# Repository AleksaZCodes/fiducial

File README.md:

# Fiducial

<!-- fid:describes thesis.toml -->
> **Build any robust multidisciplinary product with AI agents.**

That is the platform's thesis ([`thesis.toml`](thesis.toml), `fid thesis`). How:
**declare each fact once, derive every artifact from it**, and gate the result.
<!-- fid:end-describes -->

Fiducial is a cross-domain build system for products that span **web, firmware,
electronics, mechanical, simulation and content** — built at the quality and pace
that normally needs a team, by one person working with agents.

Not by working harder at each domain. By deleting the work that exists only
because the domains don't talk to each other.

---

## The problem it removes

In a cross-domain product the same fact gets written down many times:

- a **pin assignment** — in the schematic, the firmware, the test rig, the docs
- a **protocol message** — in the firmware, and again in the web client
- a **board dimension** — in the PCB tool, the enclosure model, the marketing render

Every duplicate is a place where reality drifts from itself. Drift is discovered
late, in the field, expensively.

So: **one declaration, many derivations.** The declaration is typed,
machine-readable and lives in git. Everything downstream is generated, and
generated artifacts are never hand-edited.

## The shape of the system

Three ideas stacked, and each one exists to make the one above it cheap.

```
                        ┌───────────────────────────────┐
   DECLARE              │  board.interface.json         │   typed facts,
   a fact, once         │  fiducial.toml  ·  messages/  │   inert, in git
                        └───────────────┬───────────────┘
                                        │
                                  fid derive          ← gated by --check
                                        │
        ┌───────────────┬───────────────┼───────────────┬───────────────┐
        ▼               ▼               ▼               ▼               ▼
   DERIVE          enclosure       TypeScript      wrangler.toml    migrations
   every artifact  STL · GLB       types           (deploy cfg)     SQL schema
        │
        └── never hand-edited · hashed into fiducial.lock · stale ⇒ CI fails

        firmware · desktop · browser · edge · CLI     ← many runtimes
                          ╲   │   ╱
   RUN IT ANYWHERE  fiducial-protocol                  ← one waist
                          ╱   │   ╲
        USB serial · Web Serial · WebUSB · BLE · LoRa  ← many transports
```

Logic lives as far down as it can. The `no_std` Rust spine compiles for the host,
`wasm32`, and two embedded targets **on every commit** — so a behaviour written
once runs in a browser, on a desktop, at the edge, and on a microcontroller, and
outlives every framework above it.

## A worked example

```sh
cargo install fiducial-cli

fid new my-product && cd my-product
fid add capability hardware   # one declaration → case, board, schematic, BOM, interface
fid add capability firmware-rp2040
fid derive                    # run every pipeline, hash every output
fid dash                      # roadmap, decisions, CI, pipelines, freshness
```

Declare the product once, in `hardware/product.toml`: its outline, its parts,
and what each pin connects to (an excerpt):

```toml
[[part]]
id     = "mcu"
symbol = "MCU_RaspberryPi:RP2040"
pins   = { GPIO4 = "SENSOR_SDA", GPIO5 = "SENSOR_SCL", GND = "GND" }

[[part]]
id   = "r-sda"
pick = { category = "Resistors", package = "0603", value = "4k7", has = ["1%"] }  # resolved to a real LCSC part, locked
pins = { 1 = "SENSOR_SDA", 2 = "3V3" }

[firmware]
mcu = "mcu"
```

Then `fid derive` produces — with nobody modelling, drawing or copying anything —

- the **case** around the parts, with every socket's window cut, and the
  **board** inside it: placed by a constraint solver, every pad on its net;
- the **schematic**, and the **BOM**, each part's LCSC number taken from
  `hardware/parts.lock`;
- `interface.ts` — the nets as a **TypeScript type**, for the app that talks
  to the device;
- `board.rs` — the **firmware's pin map**: `board::sensor_sda!(p)` is
  `p.PIN_4`.

`hardware/build.sh` then routes the board, builds every solid, checks that
it all fits and goes together, and writes the files a board house needs to
make and assemble it.

Move `SENSOR_SDA` to `GPIO6` and the copper, the schematic and the firmware
move with it — the firmware with no edit. Rename it, and firmware or web code
still using the old name stops compiling. Until `fid derive` has run,
`fid derive --check` names every artifact that no longer matches the
declaration and exits non-zero. It runs in CI, so an artifact that did not
follow its declaration fails the build instead of shipping. That is the whole
contract.

The whole of it, on a real product: [`examples/sensor-stick/`](examples/sensor-stick)
is a USB-C temperature and humidity stick — case, routed board, orderable fab
files, firmware and a web page from one declaration, built end to end in CI —
and [how it was made](docs/guides/sensor-stick.md), step by step.

## What you can add to it

Nothing above is special-cased into the CLI. Each of these is a **capability** —
a named, versioned extension that contributes declarations, pipelines, guard
rules and a skill for agents. `fid new` generates none of them; you add what the
product actually needs.

<!-- fid:begin capabilities -->
| Capability | Contributes | Install |
|---|---|---|
| `adapters` | declares `adapters`; 1 pipeline(s); seeds a `fiducial.toml` block | `fid add capability adapters` |
| `brand` | declares `brand`; 2 pipeline(s); 2 template file(s); seeds a `fiducial.toml` block | `fid add capability brand` |
| `cms` | declares `cms`; 1 pipeline(s); 6 template file(s); seeds a `fiducial.toml` block | `fid add capability cms` |
| `content` | declares `content.toml`, `content/posts/en/hello.md`; 1 pipeline(s); 2 template file(s) | `fid add capability content` |
| `deploy` | declares `deploy`; 1 pipeline(s); seeds a `fiducial.toml` block | `fid add capability deploy` |
| `design` | declares `design-system.md`; 1 pipeline(s); 4 template file(s) | `fid add capability design` |
| `eda` | declares `board/board.interface.json`; 2 pipeline(s); 1 template file(s) | `fid add capability eda` |
| `firmware-rp2040` | 11 template file(s); guard rules | `fid add capability firmware-rp2040` |
| `firmware-stm32` | 10 template file(s); guard rules | `fid add capability firmware-stm32` |
| `hardware` | declares `hardware/outline.svg`, `hardware/product.toml`; 1 pipeline(s); 12 template file(s) | `fid add capability hardware` |
| `i18n` | declares `i18n`, `messages/en.json`, `messages/sr.json`; 1 pipeline(s); 2 template file(s); seeds a `fiducial.toml` block | `fid add capability i18n` |
| `identity` | declares `identity`; 1 pipeline(s); seeds a `fiducial.toml` block | `fid add capability identity` |
| `legal` | declares `legal`; 1 pipeline(s); 2 template file(s); seeds a `fiducial.toml` block | `fid add capability legal` |
| `migrations` | declares `migrations`; 1 pipeline(s) | `fid add capability migrations` |
| `monitoring` | declares `monitoring.toml`; 1 pipeline(s) | `fid add capability monitoring` |
| `press` | declares `press`, `press/docs/en/boilerplate.md`, `press/docs/en/facts.md`, `press/stories/en/0001-why-this-exists.md`; 1 pipeline(s); 2 template file(s); seeds a `fiducial.toml` block | `fid add capability press` |
| `protocol` | declares `protocol.toml`; 1 pipeline(s) | `fid add capability protocol` |
| `realtime` | a skill | `fid add capability realtime` |
| `research` | declares `paper`; seeds a `fiducial.toml` block | `fid add capability research` |
| `seo` | declares `seo`; 1 pipeline(s); 2 template file(s); seeds a `fiducial.toml` block | `fid add capability seo` |
| `tauri` | 5 template file(s); guard rules | `fid add capability tauri` |
| `topology` | declares `topology.toml`; 1 pipeline(s) | `fid add capability topology` |
| `web-next` | 13 template file(s); guard rules | `fid add capability web-next` |
| `web-svelte` | 11 template file(s); guard rules | `fid add capability web-svelte` |
| `worker-cloudflare` | 1 template file(s); guard rules | `fid add capability worker-cloudflare` |
<!-- fid:end capabilities -->

### A physical product, from one file

`hardware` is the capability that goes furthest. One `hardware/product.toml`
names an outline in any SVG (a logo works), the regions on it, and the parts —
each a real KiCad symbol, footprint and STEP model, with its LCSC number and
its datasheet. `fid derive` solves the case round them, sizes and sections the
board, places its parts with a constraint solver (OR-Tools CP-SAT — every rule
a constraint, and a contradiction named rather than guessed at), wires every
pin to its net, and writes a gated layout, BOM, KiCad board and schematic. `hardware/build.sh`
then routes and DRCs the board (Freerouting), builds the solid model and fails
on any interference, unsealed joint or part that cannot go in, and exports
Gerbers, STEP and a review pack of renders. Where the vocabulary stops, a
product adds its own geometry (`hardware/shapes.py`) or its own STEP model,
and the checks still run over it.

Everything a part needs travels with it, in KiCad's own library layout:
`hardware/lib/` holds the symbols, footprints, models and datasheets (with
text copies), hash-checked, and `hardware/lib/PARTS.md` puts every part on one
page — what it is, its files, every pin's net — as the context a person or an
agent starts from.

<!-- fid:describes crates/fiducial-cli/src/adapter.rs#pub static CONTRACTS -->

Vendors sit behind **adapter contracts**, chosen per product in `[adapters]`.
Every contract ships with `none` — a real, working implementation, not a
placeholder, which is what makes it cost nothing to wire in from the first
commit. A name under *Planned* cannot be selected and fails with a message
saying so: a selectable name with nothing behind it is a promise the platform
does not keep.

Three of those `none`s **fail rather than succeed silently**: `auth`, `ai` and
`systemOne`. The difference is whether the caller reads a result. A no-op send
or enqueue is indistinguishable from the real thing at the call site — the
caller wanted an effect elsewhere. A session, a completion and a decision *are*
the result, so returning a fabricated one turns "no vendor selected" into a
logged-in stranger, a blank answer in the UI, or a confidently wrong branch
taken in production — and all three get debugged as bugs somewhere else. They
still cost nothing to wire in: constructing them is free, and nothing fails
until something actually asks.

<!-- fid:end-describes -->

<!-- fid:begin adapters -->
| Contract | For | Selectable today | Planned |
|---|---|---|---|
| `database` | Relational storage: queries, migrations, transactions | `none`, `d1`, `supabase` | `neon`, `postgres` |
| `storage` | Object storage: put, get, signed URLs | `none`, `r2`, `supabase-storage` | `s3` |
| `deploy` | Where the product ships and how a release is promoted | `none`, `cloudflare` | `vercel`, `fly` |
| `email` | Transactional email: send, template, verify a domain | `none`, `resend` | `ses`, `cloudflare-email` |
| `newsletter` | Subscriber list management: subscribe, unsubscribe, status | `none`, `resend` | — |
| `errors` | Error tracking and diagnostics | `none` | `sentry`, `workers-analytics` |
| `botProtection` | Bot / abuse challenge verification | `none`, `turnstile` | `recaptcha`, `hcaptcha` |
| `queue` | Asynchronous job/message queue (producer side) | `none`, `cloudflare-queues` | `sqs` |
| `ai` | Language-model calls: chat, streaming, tool use | `none`, `openrouter` | `workers-ai`, `anthropic`, `openai` |
| `auth` | Users and authentication: sign-up, sign-in, sessions | `none`, `supabase` | `clerk`, `auth.js` |
| `systemOne` | Typed probabilistic decisions: yes/no, one-of-N, ordered levels | `none`, `openrouter`, `typesafe` | — |
<!-- fid:end adapters -->

Both tables are generated from the registries that enforce them, by
`fid context`, and CI fails if they drift from the code.

## How you extend it

### A capability is a directory

There is no plugin API to learn and no CLI release to wait for. The **layout is
the manifest** — `fid` derives the capability from the directory, and a
third-party capability goes through the same derivation, the same conformance
checks and the same lock entry as a built-in.

```
my-capability/
├── SKILL.md              ← the only required file: how an agent uses this
├── capability.toml       ← optional: description, guard rules, [config] seed,
│                           declared directories, required adapter contracts
├── declarations/         ← typed facts, installed at the path below this dir
│   └── messages/en.json
├── pipelines/
│   └── i18n.toml         ← name, executor, args, outputs
└── anything-else         ← a plain template file, copied in, gated by nothing
```

Scaffold one, then install it from anywhere — a directory, or a git repository
pinned in `fiducial.lock` at the commit it resolved to:

```sh
fid capability new my-sensor                    # scaffold the directory above

fid add capability my-sensor --from ./capabilities/my-sensor
fid add capability stripe    --from git:https://github.com/acme/fid-stripe#v1.2.0
fid capability check                            # conformance, once installed
```

One file is a complete capability. The failure mode for an extension system is
ceremony, so `capability.toml` is optional and a capability without one takes
its description from the first line of prose in its own skill.

### The seven kinds, and why the difference is not cosmetic

<!-- fid:describes crates/fiducial-cli/src/capability/manifest.rs#pub fn derive -->

| Kind | Is | Example |
|---|---|---|
| **Declaration** | a typed fact, written once, inert — a file, a `fiducial.toml` block, or a directory the product fills | `hardware/product.toml`, the `[i18n]` block, `migrations/` |
| **Pipeline** | reads declarations, produces artifacts, **gated by `fid derive --check`** | `pipelines/hardware.toml` |
| **Adapter** | a swappable vendor behind a fixed contract | `storage = "r2"` |
| **Tool** | an external command the capability's work needs on PATH — declared, never installed | `requires_tools = ["wrangler"]` |
| **Prerequisite** | another capability this one cannot work without — checked at install, not at first failure | `requires_capabilities = ["i18n"]` |
| **Template** | a plain file copied in, belonging to no pipeline | `apps/worker/wrangler.toml` |
| **Scoped template** | a template under `for/<capability>/`, installed only alongside that capability | `for/web-svelte/…/LocalePicker.svelte` |

<!-- fid:end-describes -->

The test for a declaration: *could two different pipelines read this and both be
correct?* If yes it is a declaration; if it is one tool's config file it is a
template.

The test for a **scoped** template: *would this file be dead weight in a
product that has this capability but not the other one?* A React component in
a SvelteKit app is the case it exists for. Install order does not matter —
adding the target capability later back-fills what the others were holding.

Filing one as another is not a style mistake. A pipeline outside `pipelines/` is
installed and never runs; a `pipelines/` file listed as a template is installed
and never gated. `fid capability check` rejects both.

### A pipeline is four lines

```toml
name     = "enclosure"
executor = "fid-mesh"
args     = ["board/board.interface.json"]
outputs  = [
  "enclosure/case-base.stl",
  "enclosure/case-lid.stl",
  "enclosure/gasket.stl",
  "enclosure/case.glb",
]
```

`outputs` is what makes it gated: `fid derive` hashes each one into
`fiducial.lock`, and `fid derive --check` fails when a hash no longer matches
what the declaration implies.

`inputs` closes the other half. An output can match its hash while the file it
was derived *from* has moved — a logo redrawn, a schema another tool rewrote —
and nobody re-derived. Files listed in `inputs` (and those a built-in executor
knows it reads, such as the SVGs a `hardware/product.toml` addresses) are
hashed into the lock too, and `--check` names the one that moved.

<!-- fid:describes crates/fiducial-cli/src/commands/derive.rs#fn run_pipeline_command -->

Executors are `shell` and `cargo-test` — which need no platform change at all —
plus the in-process ones (`fid-validate`, `fid-mesh`, `fid-i18n`, `fid-brand`,
`fid-thesis`, `fid-deploy`, `fid-identity`, `fid-adapters`, `fid-schema`,
`fid-legal`, `fid-design`, `fid-protocol`, `fid-topology`, `fid-monitoring`, `fid-hardware`). Reach for `shell` first; a new in-process executor
is warranted only when the work is genuinely a Rust library call rather than a
tool invocation.

A `shell` pipeline that runs `node` runs under Node's permission model: it may
read its script's directory, its own `pipelines/<name>.toml`, its declared
`inputs` and `node_modules`, and write only where its `outputs` go. A script
that reads a file it does not declare fails naming that file, instead of
producing an output whose input the lock never recorded.

`fid-design` is the clearest case of that line: it parses a declaration, runs
OKLCH-to-sRGB conversion and WCAG contrast arithmetic over the palette, and
fails the derive when a declared pair misses its minimum. Shelling out would
mean shipping a script and a language runtime to do arithmetic the binary
already can.

<!-- fid:end-describes -->

### Adding a vendor to a contract

Implement the contract in `crates/fiducial-adapters` (and its TypeScript mirror
in `packages/adapters`), then move the vendor from `candidates` to
`implementations` in `crates/fiducial-cli/src/adapter.rs`. The table above and
the error message a user sees both derive from that one move.

One place does need the new name: `REAL_VENDORS` in
`packages/adapters/src/generated-factory.test.js`, which is the list of vendor
selections CI actually compiles the generated factory for. A vendor missing
from it is generated and never typechecked, so the suite names itself in that
comment rather than leaving it to be discovered.

Deeper detail: [`docs/specs/2026-09-15-external-capabilities.md`](./docs/specs/2026-09-15-external-capabilities.md)
and [`docs/specs/2026-09-14-capability-taxonomy.md`](./docs/specs/2026-09-14-capability-taxonomy.md).

## Documentation

**New here?** [Start here](./docs/guides/start-here.md) explains what this is and
why it is shaped that way, then [Your first product](./docs/guides/first-product.md)
takes you from nothing to a generated enclosure and a CI gate in about twenty
minutes.

| Read | For |
|---|---|
| [**docs/guides/**](./docs/guides/) | Step-by-step guides for humans and agents |
| [`AGENTS.md`](./AGENTS.md) | Working here as an agent — layout, rules, build commands |
| [`MISSION.md`](./MISSION.md) | Why this exists. The tiebreaker for ambiguous decisions. |
| [`ARCHITECTURE.md`](./ARCHITECTURE.md) | How the layers fit together. |
| [`STACK.md`](./STACK.md) | Every technology choice, enumerated. |
| [`ROADMAP.md`](./ROADMAP.md) | What is intended, in order — and so what is next. |
| [`SHIPPED.md`](./SHIPPED.md) | What was built, phase by phase. |
| [`docs/protocol/`](./docs/protocol/) | The wire specification + conformance vectors. |
| [`docs/specs/`](./docs/specs/) | Design decisions, append-only. |

Each crate and package carries its own README — start with
[`fiducial-cli`](./crates/fiducial-cli) if you want to build something, or
[`fiducial-core`](./crates/fiducial-core) if you want to see the spine.

## Repository

`firmware/` is a separate Cargo workspace (Embassy; RP2040 + STM32), and `docs/`
holds the specs, the protocol and the compatibility matrix. The two workspaces
this repository builds:

<!-- fid:begin layout -->
```
fiducial/
├── crates/               15 members
│   ├── fiducial                 Declare each fact once. Derive every artifact from it.
│   ├── fiducial-adapters        Cross-platform adapter contracts for Fiducial — database, s…
│   ├── fiducial-cli             fid — the Fiducial platform CLI
│   ├── fiducial-core            no_std spine: IDs, time primitives, validation, state machi…
│   ├── fiducial-eda             no_std EDA pipeline types — the BoardInterface schema for b…
│   ├── fiducial-geometry        no_std geometry for Fiducial: points, tolerance profiles, c…
│   ├── fiducial-identity        no_std identity spine: one Principal across users, devices…
│   ├── fiducial-mesh            no_std case generation from a board outline: gasket-sealed…
│   ├── fiducial-model           no_std Fact, Decision and Pipeline contract types.
│   ├── fiducial-ota             no_std over-the-air firmware update protocol: signed manife…
│   ├── fiducial-protocol        no_std transport-agnostic protocol: framing, checksums, seq…
│   ├── fiducial-quantity        no_std typed quantities with tolerance algebra and assertions.
│   ├── fiducial-sim             Numerical simulation — ODE integration that runs native (wi…
│   ├── fiducial-tauri           Serial transport and device discovery for Fiducial Tauri apps.
│   └── fiducial-wasm            WASM bindings for fiducial-core — browser, edge, and Cloudf…
└── packages/             13 members
    ├── adapters                 Cross-platform adapter contracts for Fiducial — database, s…
    ├── advisor                  Advisory checks for Fiducial — typed judgments where determ…
    ├── board-schema             TypeScript types for board.interface.json — mirrors the Rus…
    ├── cli                      fid — the Fiducial platform CLI
    ├── fiducial                 Declare each fact once. Derive every artifact from it.
    ├── headless                 Framework-agnostic headless utilities for Fiducial — Result…
    ├── i18n                     Localized by construction — typed message keys, locale nego…
    ├── identity                 One identity model across users, devices and services — mir…
    ├── realtime                 Supabase Realtime typed wrappers — Broadcast, Presence, and…
    ├── tokens                   Design tokens for Fiducial — OKLCH theme vars, Tailwind v4…
    ├── transport-web            Web Serial, WebUSB, and BLE transports for Fiducial — same…
    ├── viewer3d-react           React component for rendering Fiducial board GLB files in a…
    └── wasm-bridge              Generated TypeScript types for the fiducial WASM boundary.
```
<!-- fid:end layout -->

## License

MIT — see [`LICENSE`](./LICENSE).

Product repos, domain logic, novel protocols and hardware designs are private;
see [`IP-POLICY.md`](./IP-POLICY.md).

Contributions are welcome and need a sign-off — see [`CLA.md`](./CLA.md). It
exists so the project keeps the option to relicense later: that option is
destroyed silently by the first contribution merged without one, and cannot be
recovered afterwards.

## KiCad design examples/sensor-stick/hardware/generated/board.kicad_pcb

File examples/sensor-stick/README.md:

# sensor-stick

A USB-C stick that reports room temperature and humidity to a web page — a
whole product, from one declaration, built with
[Fiducial](https://github.com/AleksaZCodes/fiducial) and checked in its CI.

It is the platform's worked example: small and cheap (an RP2040, an AHT20
sensor, a WS2812B LED behind a 5 V buffer, a USB-C socket: 23 parts, $4.74
of them per board at five boards, LCSC's prices with minimum orders, checked
against a $15 ceiling on every derive; the printed case and the vent are not
priced), but it carries every discipline a product has — a printed case, a
routed board, firmware and a web page — and every one of them is derived
from, or checked against, the same facts.

**Status: designed and checked, not built.** Every part is a real,
orderable part, the board routes and passes KiCad's DRC, the firmware
compiles and the page type-checks. Nobody has ordered it, soldered it or
plugged it in. What would be learnt on the bench is not claimed here.

| | | |
|---|---|---|
|  |  |  |
| assembled: 36 × 84 × 15.5 mm, the USB-C socket flush with the case at one end, the sensor's vent at the other | the routed board in the base: the sensor alone at the far end, under its chimney | lid, board, base |

Renders from `hardware/build.sh`, copied to `hardware/showcase/`.

## What a person writes

| File | Is |
|---|---|
| [`hardware/product.toml`](hardware/product.toml) | the product: its outline, its case, every part (an LCSC number, a KiCad symbol and footprint) and what each pin connects to |
| [`hardware/outline.svg`](hardware/outline.svg) | the stick's shape, seen from above |
| [`hardware/vendor/`](hardware/vendor) | parts KiCad has no entry or no 3D model for, from LCSC's library (`parts.py fetch`), and the USB-C socket: KiCad's land pattern with LCSC's model on it, with where each came from |
| [`firmware/rp2040/src/main.rs`](firmware/rp2040/src/main.rs), [`firmware/shared/src/lib.rs`](firmware/shared/src/lib.rs) | the firmware: read the sensor once a second, send the reading as a fiducial-protocol frame over USB serial, colour the LED |
| [`web/src/`](web/src) | the page: connect over Web Serial, show the reading |
| [`protocol.toml`](protocol.toml) | the reading's payload — its kind byte and fields — declared once for both sides of the USB link |

## What is derived from it

`fid derive` (gated by `fid derive --check`):

| File | Is |
|---|---|
| `hardware/generated/layout.json` | every position and size, and `why` — what set each |
| `hardware/generated/placement.json` | the board placement, solved by a constraint solver (CP-SAT) |
| `hardware/generated/board.kicad_pcb`, `board.kicad_sch` | the board with every footprint placed and every pad on its net; the schematic |
| `hardware/generated/bom.csv`, `assembly.md` | the bill of materials; the order it goes together in |
| `hardware/generated/interface.ts` | the nets as a TypeScript type — the page imports it |
| `hardware/generated/board.rs` | the firmware's pin map: `board::sensor_sda!(p)` is `p.PIN_4` — the firmware takes every pin through it, and a pin named directly fails derive |
| `protocol/messages.rs`, `protocol/messages.ts` | the reading's encoder for the firmware and decoder for the page, from the same table — they cannot disagree |
| `hardware/generated/assembly.md` → why | the USB-C CC voltage each kind of source reads, solved from the pull-downs and checked against the Type-C spec's window — a wrong resistor fails derive |

`hardware/build.sh` (built, checked, not committed): the routed and
DRC-checked board, the case as STEP and STL, the fit and assembly checks,
and `hardware/build/fab/` — Gerbers, the assembly BOM and the placement file
a board house takes.

`python3 hardware/parts.py resolve` checked every LCSC number against LCSC's
own record of it and wrote what it found to `hardware/parts.lock`.

## Change one thing

Move the sensor's data line from `GPIO4` to `GPIO6` in `product.toml`:

1. `fid derive --check` fails: the board, the schematic, the interface and
   `board.rs` no longer match the declaration.
2. `fid derive` moves the copper, relabels the schematic and rewrites
   `board.rs`.
3. The firmware does not compile — and should not: GPIO6 is not one of
   I2C0's SDA pins, and Embassy's types say so. Move it to `GPIO8` instead
   (I2C0 SDA) and the firmware compiles with no edit to it.

Rename the net `SENSOR_SDA` and every line of firmware or page code that
still uses the old name stops compiling. Nothing is copied by hand, so
nothing can be left behind.

## Build it

```sh
fid derive                                   # the gated artifacts
python3 hardware/parts.py sync               # vendor symbols, footprints, models
hardware/build.sh                            # route, solids, checks, fab files, renders
(cd firmware/rp2040 && cargo build --release) # the firmware (thumbv6m-none-eabi)
(cd firmware && cargo test -p firmware-shared --target x86_64-unknown-linux-gnu)
node --experimental-strip-types --test web/src/reading.test.ts
npx esbuild web/src/main.ts --bundle --format=esm --outfile=web/dist/main.js --tsconfig=web/tsconfig.json
```

Then serve `web/` and open `index.html` in Chrome or Edge.

The first flash needs no programmer: an RP2040 with empty flash starts its
USB bootloader, and `elf2uf2-rs` or `picotool` copies the firmware across.

## How it was made

With the commands above and an agent: the walk-through, step by step — what
was typed, what the agent changed, what the gates refused and why — is
[`docs/guides/sensor-stick.md`](../../docs/guides/sensor-stick.md).

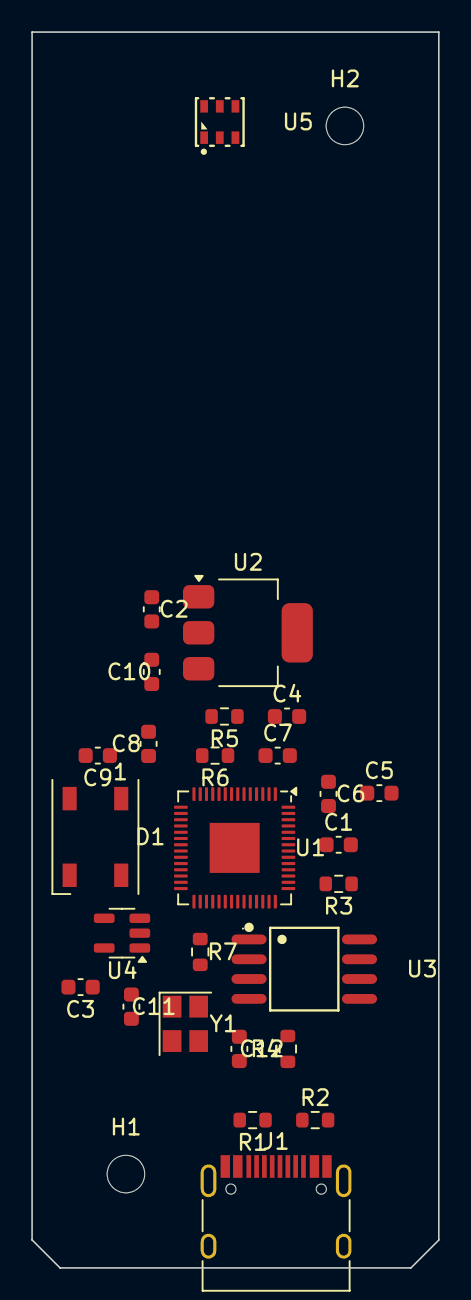
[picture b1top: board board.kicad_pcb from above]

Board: 2 copper layers, 26.0 x 79.0 mm, 29 parts (0 on the bottom side), 23 nets, no tracks yet.

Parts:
C1, C2, C3, C4, C5, C6, C7, C8, C9, C10, C11, C12: C_0603_1608Metric
D1: LED_WS2812B_PLCC4_5.0x5.0mm_P3.2mm
H1, H2: MountingHole
J1: USB_C_Receptacle_HRO_TYPE-C-31-M-12
R1, R2, R3, R4, R5, R6, R7: R_0603_1608Metric
U1: QFN-56-1EP_7x7mm_P0.4mm_EP3.2x3.2mm
U2: SOT-223-3_TabPin2
U3: SOIC-8_L5.3-W5.3-P1.27-LS8.0-BL
U4: SOT-23-5
U5: SENSOR-SMD_L3.0-W3.0-P1.00-BR
Y1: Crystal_SMD_3225-4Pin_3.2x2.5mm

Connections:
1V1: C1.1, U1.23, U1.45, U1.50
3V3: C2.1, C4.1, C5.1, C6.1, C7.1, C8.1, R5.2, R6.2, U1.1, U1.10, U1.22, U1.33, U1.42, U1.43, U1.44, U1.48, U1.49, U2.2, U3.8, U5.2
CC1: J1.A5, R1.1
CC2: J1.B5, R2.1
GND: C1.2, C2.2, C3.2, C4.2, C5.2, C6.2, C7.2, C8.2, C9.2, C10.2, C11.2, C12.2, D1.3, J1.A1, J1.A12, J1.B1, J1.B12, J1.S1, R1.2, R2.2, U1.19, U1.57, U2.1, U3.4, U4.1, U4.3, U5.5, Y1.2, Y1.4
LED_DIN: U1.27, U4.2
LED_DIN_5V: D1.4, U4.4
QSPI_SCLK: U1.52, U3.6
QSPI_SD0: U1.53, U3.5
QSPI_SD1: U1.55, U3.2
QSPI_SD2: U1.54, U3.3
QSPI_SD3: U1.51, U3.7
QSPI_SS: U1.56, U3.1
SENSOR_SCL: R5.1, U1.7, U5.3
SENSOR_SDA: R6.1, U1.6, U5.4
USB_DM: J1.A7, J1.B7, R3.1
USB_DM_MCU: R3.2, U1.46
USB_DP: J1.A6, J1.B6, R4.1
USB_DP_MCU: R4.2, U1.47
VBUS: C3.1, C9.1, C10.1, D1.1, J1.A4, J1.A9, J1.B4, J1.B9, U2.3, U4.5
XIN: C11.1, U1.20, Y1.1
XOUT: R7.1, U1.21
XOUT_X: C12.1, R7.2, Y1.3
